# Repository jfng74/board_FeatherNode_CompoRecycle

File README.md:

# board_FeatherNode_CompoRecycle

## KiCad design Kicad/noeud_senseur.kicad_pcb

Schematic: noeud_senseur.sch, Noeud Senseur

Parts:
Adafruit_Feather-1: FEATHER_MO_LORA
D1, D2: LED; LED-5MM
JP1: Jumper; Pin_Header_Straight_1x02_Pitch2.54mm
Q1, Q2: DMG1012UW; SOT-23_Handsoldering
Q3: LP0701_SGD; TO-92_Inline_Narrow_Oval
R1, R2: 1k; R_0805_HandSoldering
R3: 50k; R_0805_HandSoldering
R4, R6: 2.2k; R_0805_HandSoldering
R5: 4.7k; R_0805_HandSoldering
S1: ORD211-1015; Pin_Header_Straight_1x02_Pitch2.54mm
U2: DS18B20; TO-92_Inline_Wide

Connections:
+3V3: Adafruit_Feather-1.14 (ARf), Adafruit_Feather-1.15 (3V3), R1.1, R2.1, R4.1, R5.1, R6.1, U2.3 (VDD); also elsewhere on the board
/1_WIRE_IO: Adafruit_Feather-1.22 (D5), R5.2, U2.2 (DQ); also elsewhere on the board
/A0: Adafruit_Feather-1.12 (A0); also elsewhere on the board
/A1: Adafruit_Feather-1.11 (A1); also elsewhere on the board
/A2: Adafruit_Feather-1.10 (A2); also elsewhere on the board
/A3: Adafruit_Feather-1.9 (A3); also elsewhere on the board
/A4: Adafruit_Feather-1.8 (A4); also elsewhere on the board
/A5: Adafruit_Feather-1.7 (A5); also elsewhere on the board
/I2C/INT_SQW: JP1.2, Q3.2 (G), R3.1, S1.1; also elsewhere on the board
/LED_1: Adafruit_Feather-1.26 (D11), Q1.1 (G)
/LED_2: Adafruit_Feather-1.27 (D12), Q2.1 (G)
/MCP2515_CS: Adafruit_Feather-1.24 (D9); also elsewhere on the board
/MCP2515_INT: Adafruit_Feather-1.23 (D6), JP1.1; also elsewhere on the board
/MISO: Adafruit_Feather-1.4 (MISO); also elsewhere on the board
/MOSI: Adafruit_Feather-1.5 (MOSI); also elsewhere on the board
/RX: Adafruit_Feather-1.3 (RX0); also elsewhere on the board
/SCK: Adafruit_Feather-1.6 (SCK); also elsewhere on the board
/SCL: Adafruit_Feather-1.21 (SCL), R4.2; also elsewhere on the board
/SDA: Adafruit_Feather-1.20 (SDA), R6.2; also elsewhere on the board
/SD_CS: Adafruit_Feather-1.25 (D10); also elsewhere on the board
/TX: Adafruit_Feather-1.2 (TX1); also elsewhere on the board
/VBAT_FEATHER: Adafruit_Feather-1.29 (VUSB), Q3.1 (S), R3.2; also elsewhere on the board
GND: Adafruit_Feather-1.13 (GND), Q1.2 (S), Q2.2 (S), S1.2, U2.1 (GND); also elsewhere on the board
unnamed: Adafruit_Feather-1.30 (EN), Q3.3 (D)
unnamed: D1.1, Q1.3 (D)
unnamed: D1.2, R1.2
unnamed: D2.1, Q2.3 (D)
unnamed: D2.2, R2.2

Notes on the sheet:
R3 : Pull Up de 50k à 100k

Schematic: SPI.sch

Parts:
C1, C4, C5, C6: 0.1uF; C_0805_HandSoldering
C2, C3: 10pF; C_0805_HandSoldering
C12: 1uF; C_0805_HandSoldering
R23: 10k; R_0805_HandSoldering
U4: SN65HVD232Q; SOIC-8_3.9x4.9mm_Pitch1.27mm
U5: MCP2515; SOIC-18W_7.5x11.6mm_Pitch1.27mm
Y1: 16MHz; SMD-2520
uSD-1: Micro_SD_Card_no_shield; 114-00841-68

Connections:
+3V3: C1.2, C4.1, C5.1, C6.1, C12.1, R23.1, U4.3 (VDD), U5.18 (VDD), uSD-1.4 (VDD); also elsewhere on the board
/Connect/CAN+: U4.7 (CANH); also elsewhere on the board
/Connect/CAN-: U4.6 (CANL); also elsewhere on the board
/MCP2515_CS: U5.16 (~CS); also elsewhere on the board
/MCP2515_INT: U5.12 (~INT); also elsewhere on the board
/MISO: U5.15 (SO), uSD-1.7 (DAT0); also elsewhere on the board
/MOSI: U5.14 (SI), uSD-1.3 (CMD); also elsewhere on the board
/SCK: U5.13 (SCK), uSD-1.5 (CLK); also elsewhere on the board
/SD_CS: uSD-1.2 (DAT3/CD); also elsewhere on the board
/SPI/RXC: U4.4 (RXD), U5.2 (RXCAN)
/SPI/TXC: U4.1 (TXD), U5.1 (TXCAN)
GND: C1.1, C2.2, C3.2, C4.2, C5.2, C6.2, C12.2, U4.2 (VSS), U5.9 (VSS), uSD-1.6 (VSS); also elsewhere on the board
unnamed: C2.1, U5.7 (OSC2), Y1.2
unnamed: C3.1, U5.8 (OSC1), Y1.1
unnamed: R23.2, U5.17 (~RESET)

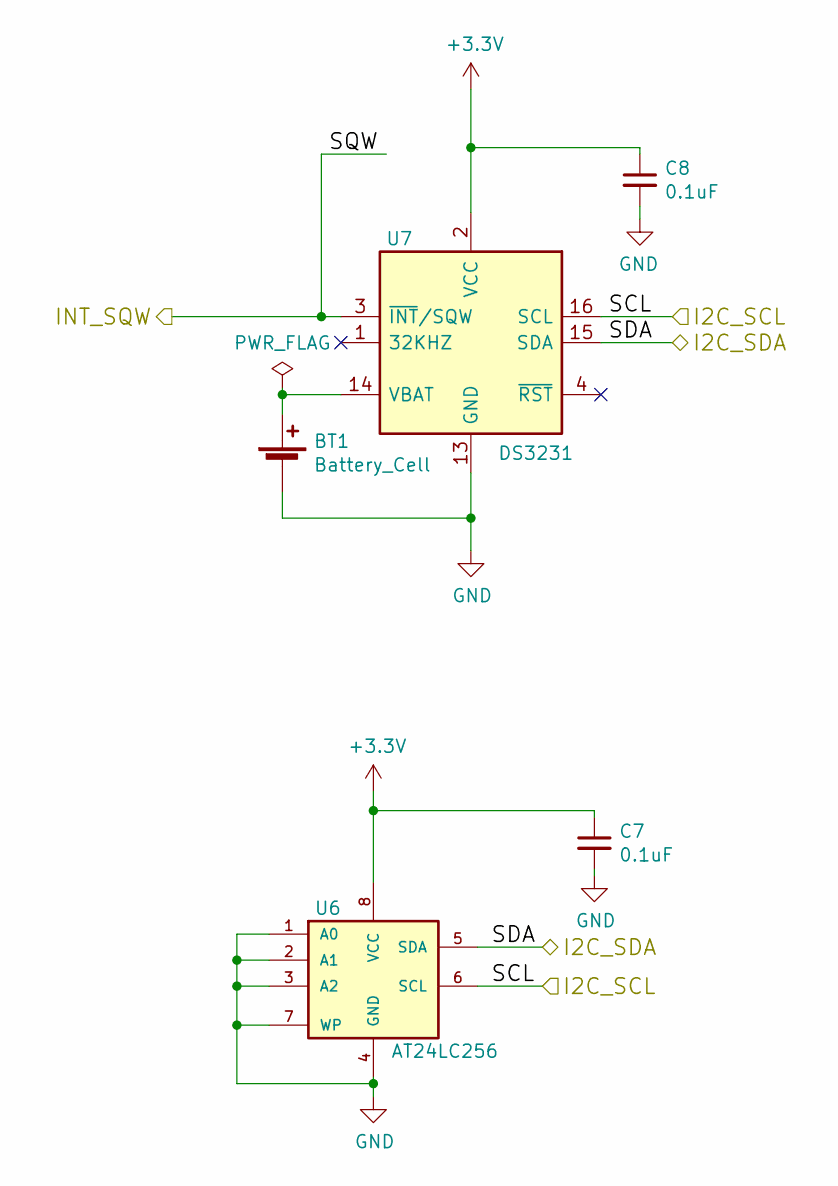
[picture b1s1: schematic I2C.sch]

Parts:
BT1: Battery_Cell; BS-7
C7, C8: 0.1uF; C_0805_HandSoldering
U6: AT24LC256; SOIJ-8_5.3x5.3mm_Pitch1.27mm
U7: DS3231; SOIC-16W_7.5x10.3mm_Pitch1.27mm

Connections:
+3V3: C7.1, C8.1, U6.8 (VCC), U7.2 (VCC); also elsewhere on the board
/I2C/INT_SQW: U7.3 (~INT~/SQW); also elsewhere on the board
/SCL: U6.6 (SCL), U7.16 (SCL); also elsewhere on the board
/SDA: U6.5 (SDA), U7.15 (SDA); also elsewhere on the board
GND: BT1.2 (-), C7.2, C8.2, U6.1 (A0), U6.2 (A1), U6.3 (A2), U6.4 (GND), U6.7 (WP), U7.5 (NC), U7.6 (NC), U7.7 (NC), U7.8 (NC), U7.9 (NC), U7.10 (NC), U7.11 (NC), U7.12 (NC), U7.13 (GND); also elsewhere on the board
unnamed: BT1.1 (+), U7.14 (VBAT)

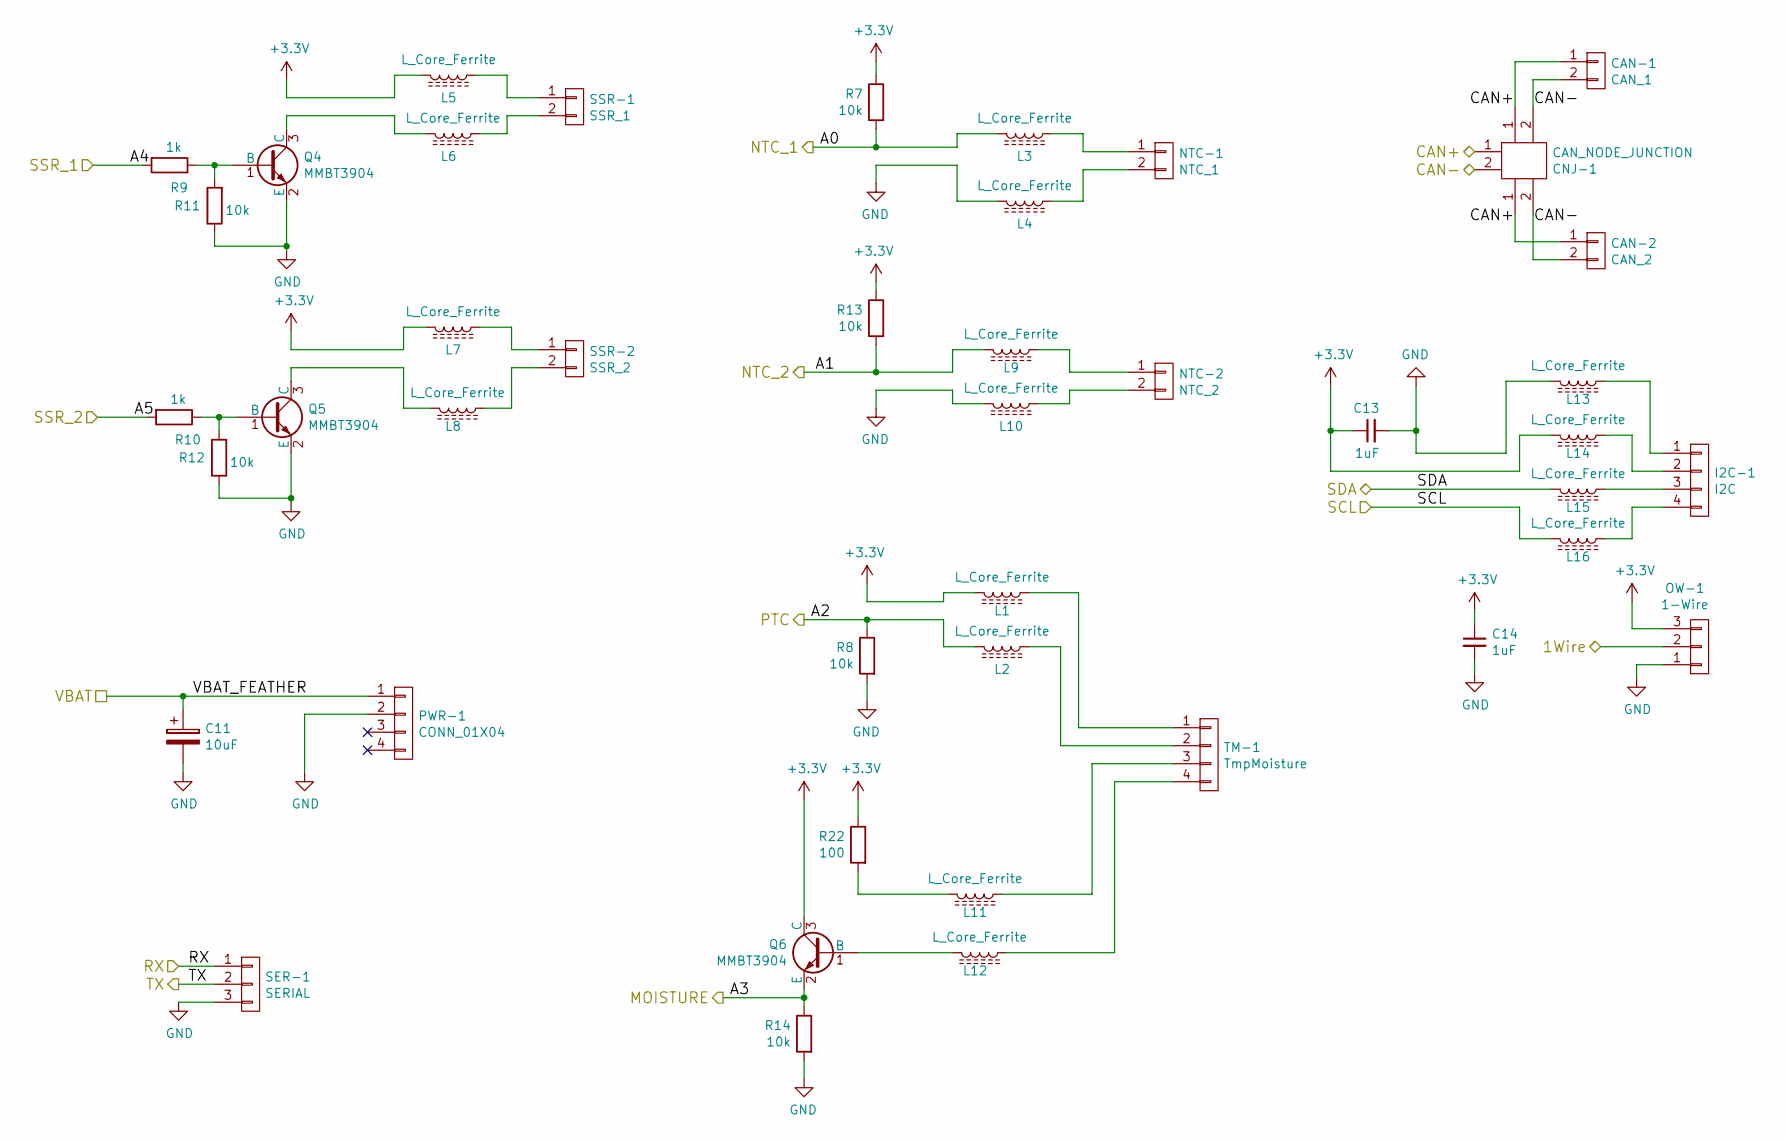
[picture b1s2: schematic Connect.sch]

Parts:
C11: 10uF; CP_Elec_4x4.5
C13, C14: 1uF; C_0805_HandSoldering
CAN-1: CAN_1; 0436500219
CAN-2: CAN_2; 0436500219
CNJ-1: CAN_NODE_JUNCTION; CAN_NODE_JONCTION
I2C-1: I2C; 0436500417
L1, L2, L3, L4, L5, L6, L7, L8, L9, L10, L11, L12, L13, L14, L15, L16: L_Core_Ferrite; R_0805_HandSoldering
NTC-1: NTC_1; Molex_KK-6410-02_02x2.54mm_Straight
NTC-2: NTC_2; Molex_KK-6410-02_02x2.54mm_Straight
OW-1: 1-Wire; 0436500317
PWR-1: CONN_01X04; 0430450428
Q4, Q5, Q6: MMBT3904; SOT-23_Handsoldering
R7, R8, R11, R12, R13, R14: 10k; R_0805_HandSoldering
R9, R10: 1k; R_0805_HandSoldering
R22: 100; R_0805_HandSoldering
SER-1: SERIAL; Molex_KK-6410-03_03x2.54mm_Straight
SSR-1: SSR_1; Molex_KK-6410-02_02x2.54mm_Straight
SSR-2: SSR_2; Molex_KK-6410-02_02x2.54mm_Straight
TM-1: TmpMoisture; Molex_KK-6410-04_04x2.54mm_Straight

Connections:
+3V3: C13.1, C14.1, L1.2, L5.2, L7.2, L14.2, OW-1.3, Q6.3 (C), R7.1, R13.1, R22.1; also elsewhere on the board
/1_WIRE_IO: OW-1.2; also elsewhere on the board
/A0: L3.2, R7.2; also elsewhere on the board
/A1: L9.2, R13.2; also elsewhere on the board
/A2: L2.2, R8.1; also elsewhere on the board
/A3: Q6.2 (E), R14.1; also elsewhere on the board
/A4: R9.2; also elsewhere on the board
/A5: R10.2; also elsewhere on the board
/Connect/CAN+: CAN-1.1, CAN-2.1, CNJ-1.1; also elsewhere on the board
/Connect/CAN-: CAN-1.2, CAN-2.2, CNJ-1.2; also elsewhere on the board
/RX: SER-1.1; also elsewhere on the board
/SCL: L16.2; also elsewhere on the board
/SDA: L15.2; also elsewhere on the board
/TX: SER-1.2; also elsewhere on the board
/VBAT_FEATHER: C11.1, PWR-1.1; also elsewhere on the board
GND: C11.2, C13.2, C14.2, L4.2, L10.2, L13.2, OW-1.1, PWR-1.2, Q4.2 (E), Q5.2 (E), R8.2, R11.1, R12.1, R14.2, SER-1.3; also elsewhere on the board
unnamed: I2C-1.1, L13.1
unnamed: I2C-1.2, L14.1
unnamed: I2C-1.3, L15.1
unnamed: I2C-1.4, L16.1
unnamed: L1.1, TM-1.1
unnamed: L2.1, TM-1.2
unnamed: L3.1, NTC-1.1
unnamed: L4.1, NTC-1.2
unnamed: L5.1, SSR-1.1
unnamed: L6.1, SSR-1.2
unnamed: L6.2, Q4.3 (C)
unnamed: L7.1, SSR-2.1
unnamed: L8.1, SSR-2.2
unnamed: L8.2, Q5.3 (C)
unnamed: L9.1, NTC-2.1
unnamed: L10.1, NTC-2.2
unnamed: L11.1, TM-1.3
unnamed: L11.2, R22.2
unnamed: L12.1, TM-1.4
unnamed: L12.2, Q6.1 (B)
unnamed: Q4.1 (B), R9.1, R11.2
unnamed: Q5.1 (B), R10.1, R12.2

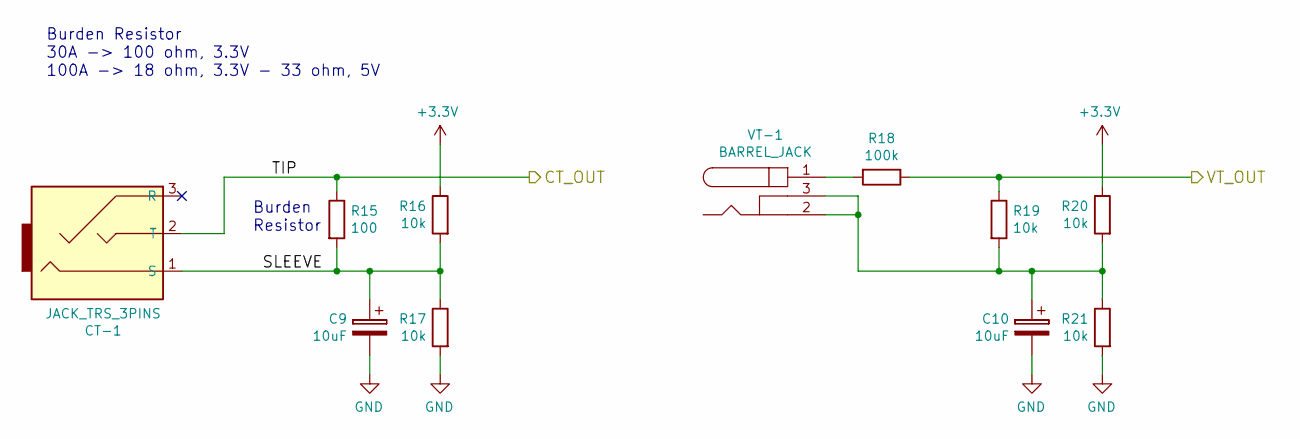
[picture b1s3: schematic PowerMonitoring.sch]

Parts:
C9, C10: 10uF; CP_Elec_4x4.5
CT-1: JACK_TRS_3PINS; SJ1-3523N
R15: 100; R_0805_HandSoldering
R16, R17, R19, R20, R21: 10k; R_0805_HandSoldering
R18: 100k; R_0805_HandSoldering
VT-1: BARREL_JACK; Molex_KK-6410-03_03x2.54mm_Straight

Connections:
+3V3: R16.1, R20.1; also elsewhere on the board
/A2: CT-1.2 (T), R15.1; also elsewhere on the board
/A3: R18.1, R19.1; also elsewhere on the board
/PowerMonitoring/SLEEVE: C9.1, CT-1.1 (S), R15.2, R16.2, R17.1
GND: C9.2, C10.2, R17.2, R21.2; also elsewhere on the board
unnamed: C10.1, R19.2, R20.2, R21.1, VT-1.2, VT-1.3
unnamed: R18.2, VT-1.1

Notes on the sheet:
Burden Resistor
Burden Resistor 30A -> 100 ohm, 3.3V 100A -> 18 ohm, 3.3V - 33 ohm, 5V

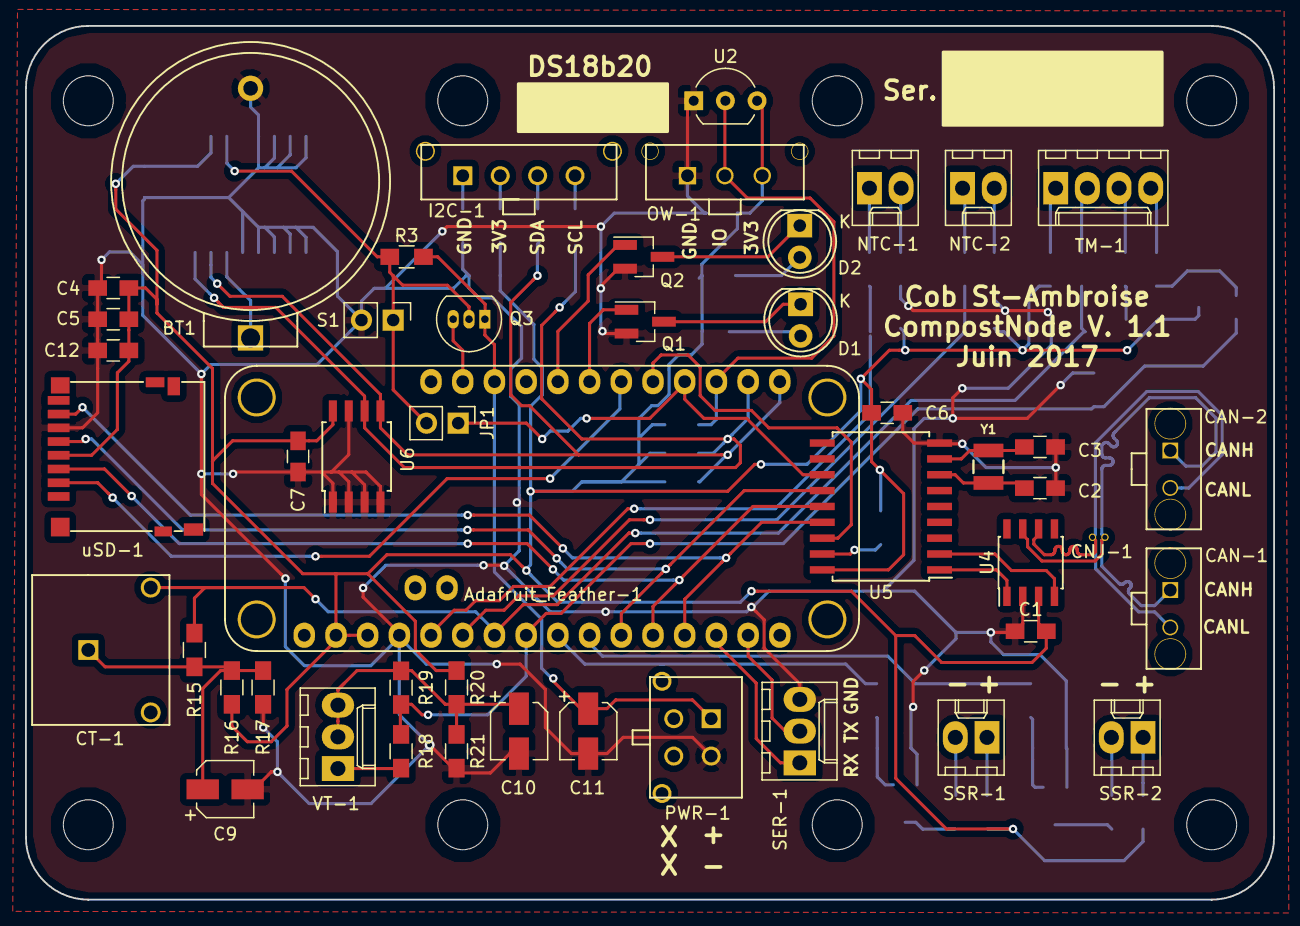
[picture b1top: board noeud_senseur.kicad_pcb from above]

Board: 2 copper layers, 100.0 x 70.0 mm, 86 parts (0 on the bottom side), 61 nets.

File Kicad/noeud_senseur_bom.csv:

Component,Description,Part,References,Value,Footprint,Quantity Per PCB,Datasheet
1,,FEATHER_MO_LORA,Adafruit_Feather-1,FEATHER_MO_LORA,FEATHER_MO_LORA,1,
2,single battery cell,Battery_Cell,BT1,Battery_Cell,BS-7,1,
3,Unpolarized capacitor,C_Small,C1 C4 C5 C6 C7 C8 C12 C13 C14,0.1uF,C_0805_HandSoldering,9,
4,Unpolarized capacitor,C_Small,C2 C3,10pF,C_0805_HandSoldering,2,
5,Polarised capacitor,CP,C9 C10 C11,10uF,CP_Elec_4x4.5,3,
6,"Connector, single row, 01x02, pin header",CONN_01X02,CAN-1,CAN_1,0436500219,1,
7,"Connector, single row, 01x02, pin header",CONN_01X02,CAN-2,CAN_2,0436500219,1,
8,"Connector, single row, 01x02",CAN_NODE_JUNCTION,CNJ-1,CAN_NODE_JUNCTION,CAN_NODE_JONCTION,1,
9,audio jack TRS 6 pins,JACK_TRS_3PINS,CT-1,JACK_TRS_3PINS,SJ1-3523N,1,
10,LED generic,LED,D1 D2,LED,LED-5MM,2,
11,"Connector, single row, 01x04, pin header",CONN_01X04,I2C-1,I2C,0436500417,1,
12,Inductor with Ferrite Core,L_Core_Ferrite,L1 L2 L3 L4 L5 L6 L7 L8 L9 L10 L11 L12 L13 L14 L15 L16,L_Core_Ferrite,R_0805_HandSoldering,16,
13,"Connector, single row, 01x02, pin header",CONN_01X02,NTC-1,NTC_1,Molex_KK-6410-02_02x2.54mm_Straight,1,
14,"Connector, single row, 01x02, pin header",CONN_01X02,NTC-2,NTC_2,Molex_KK-6410-02_02x2.54mm_Straight,1,
15,"Connector, single row, 01x03, pin header",CONN_01X03,OW-1,1-Wire,0436500317,1,
16,"Connector, single row, 01x04, pin header",CONN_01X04,PWR-1,CONN_01X04,0430450428,1,
17,"60V Vds, 0.115A Id, N-channel MOSFET, SOT-23",DMG1012T,Q1 Q2,DMG1012UW,SOT-23_Handsoldering,2,https://www.fairchildsemi.com/datasheets/2N/2N7002.pdf
18,Transistor P-MOSFET with substrate diode (general),Q_PMOS_SGD,Q3,LP0701_SGD,TO-92_Inline_Narrow_Oval,1,
19,"45V Vce, 0.8A Ic, NPN, SOT-23",MMBT3904,Q4 Q5 Q6,MMBT3904,SOT-23_Handsoldering,3,http://www.fairchildsemi.com/ds/BC/BC817.pdf
20,Resistor,R,R15 R22,100,R_0805_HandSoldering,2,
21,Resistor,R,R18,100k,R_0805_HandSoldering,1,
22,Resistor,R,R7 R8 R11 R12 R13 R14 R16 R17 R19 R20 R21,10k,R_0805_HandSoldering,11,
23,Resistor,R,R1 R2 R9 R10,1k,R_0805_HandSoldering,4,
24,Resistor,R,R4 R6,2.2k,R_0805_HandSoldering,2,
25,Resistor,R,R5,4.7k,R_0805_HandSoldering,1,
26,Resistor,R,R3,50k,R_0805_HandSoldering,1,
27,,ORD211-1015,S1,ORD211-1015,Pin_Header_Straight_1x02_Pitch2.54mm,1,
28,"Connector, single row, 01x03, pin header",CONN_01X03,SER-1,SERIAL,Molex_KK-6410-03_03x2.54mm_Straight,1,
29,"Connector, single row, 01x02, pin header",CONN_01X02,SSR-1,SSR_1,Molex_KK-6410-02_02x2.54mm_Straight,1,
30,"Connector, single row, 01x02, pin header",CONN_01X02,SSR-2,SSR_2,Molex_KK-6410-02_02x2.54mm_Straight,1,
31,"Connector, single row, 01x04, pin header",CONN_01X04,TM-1,TmpMoisture,Molex_KK-6410-04_04x2.54mm_Straight,1,
32,"32Kb (4096x8) Serial EEPROM with Unique Serial Number, SO8",AT24LC256,U6,AT24LC256,SOIJ-8_5.3x5.3mm_Pitch1.27mm,1,http://www.atmel.com/Images/Atmel-8869-SEEPROM-AT24CS32-Data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
33,,DS18B20,U2,DS18B20,TO-92_Inline_Wide,1,
34,Extremely Accurate I2C-Integrated RTC/TCXO/Crystal SOIC-16,DS3231,U7,DS3231,SOIC-16W_7.5x10.3mm_Pitch1.27mm,1,http://datasheets.maximintegrated.com/en/ds/DS3231.pdf
35,,MCP2515,U5,MCP2515,SOIC-18W_7.5x11.6mm_Pitch1.27mm,1,
36,,SN65HVD232Q,U4,SN65HVD232Q,SOIC-8_3.9x4.9mm_Pitch1.27mm,1,
37,DC Barrel Jack,BARREL_JACK,VT-1,BARREL_JACK,Molex_KK-6410-03_03x2.54mm_Straight,1,
38,"Two pin crystal, small symbol",Crystal_Small,Y1,16MHz,SMD-2520,1,
39,Micro SD Card Socket,Micro_SD_Card_no_shield,uSD-1,Micro_SD_Card_no_shield,114-00841-68,1,http://katalog.we-online.de/em/datasheet/693072010801.pdf





Component Groups:,39
Component Count:,84
Fitted Components:,84
Number of PCBs:,1
Total components:,84
Schematic Version:,
Schematic Date:,2017-02-23
BoM Date:,lun 08 mai 2017 14:56:23 EDT
Schematic Source:,/home/caribou/git_rep/board_FeatherNode_CompoRecycle/Kicad/noeud_senseur.sch
KiCad Version:,Eeschema no-vcs-found-01f5a12~58~ubuntu16.04.1

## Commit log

2017-05-16 Ajout du repertoire Applications
2017-05-16 Ajout du repertoire Kicad
2017-05-16 Ajout du repertoire Application + les gitignore
2017-05-17 ajout de la librarie DS3231
2017-05-17 Mise a jour de node_feather_compost.cpp
2017-05-17 Mise a jour de node_feather_compost.h
2017-05-17 retrait du define de BME280
2017-05-17 mise a jour de platform.ini
2017-05-17 Mise a jour de main.cpp
2017-05-24 mise a jour du fichier node_feather_compost.h
2017-05-24 mise a jour de FanCompostMsg.h
2017-05-24 Ajout de FanCompostMsg.h
2017-05-24 mise a jour
2017-05-24 Ajout de l'impression de la date
2017-05-24 Ajout de l'impression d'heure
2017-05-24 ajout fonction ajustement de clock
2017-05-24 ajout de fonction d'ajustement d'heure
2017-05-24 ajout de fonction d'ajustement de l'heure
2017-05-24 fonction d'ajout d'ajustement d<heure
2017-05-25 finale du 24 mai
2017-06-14 Mise a jour de main pour fonctionner avec FeatherNodeFanController
2017-07-06 Mise a jour du 6 juillet 2017
2017-07-11 Modification des fichiers platform.ini
2017-07-19 Grosse mise a jour...
2018-01-28 Ajout d'une 5 ieme consigne
2018-01-28 Recompilation des applications.
